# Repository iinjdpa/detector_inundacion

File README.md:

# detector_inundacion
Detector de inundacion con ESP8266 usando pilas

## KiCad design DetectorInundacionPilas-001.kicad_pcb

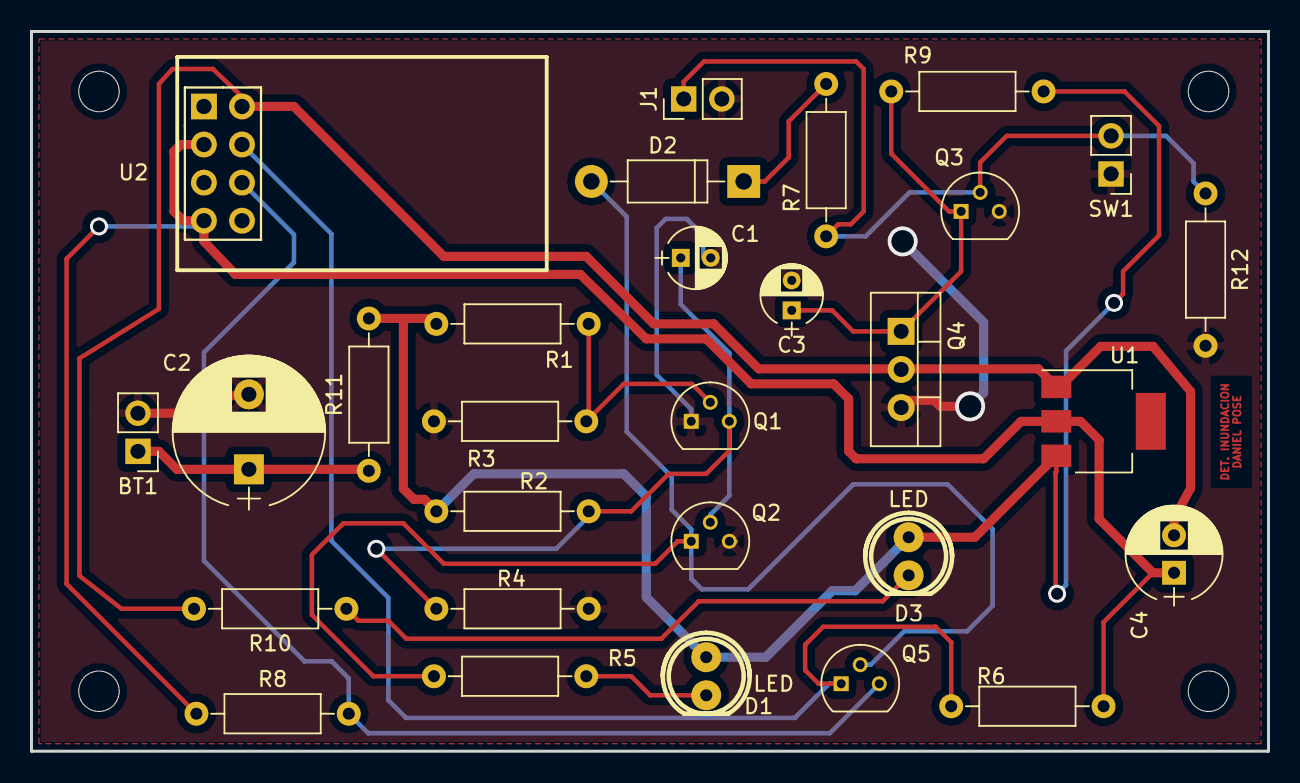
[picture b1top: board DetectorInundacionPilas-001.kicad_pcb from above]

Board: 2 copper layers, 82.5 x 48.0 mm, 29 parts (0 on the bottom side), 15 nets.

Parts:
BT1: 4xAA; Pin_Header_Straight_1x02_Pitch2.54mm
C1: 100uF; CP_Radial_D4.0mm_P2.00mm
C2: 1000uF; CP_Radial_D10.0mm_P5.00mm
C3: 0.1uF; CP_Radial_D4.0mm_P2.00mm
C4: 470uF; CP_Radial_D6.3mm_P2.50mm
D1: LED; led_5mm_red
D2: 1N4007; D_DO-41_SOD81_P10.16mm_Horizontal
D3: LED; led_5mm_green
J1: Sensor agua; Pin_Header_Straight_1x02_Pitch2.54mm
Q1: 2N7000; TO-92_Molded_Narrow
Q2, Q3, Q5: BS170; TO-92_Molded_Narrow
Q4: IRFZ44; TO-220-3_Vertical
R1: 270K; R_Axial_DIN0207_L6.3mm_D2.5mm_P10.16mm_Horizontal
R2, R3: 100K; R_Axial_DIN0207_L6.3mm_D2.5mm_P10.16mm_Horizontal
R4: 1M; R_Axial_DIN0207_L6.3mm_D2.5mm_P10.16mm_Horizontal
R5: 470; R_Axial_DIN0207_L6.3mm_D2.5mm_P10.16mm_Horizontal
R6, R8: 4K7; R_Axial_DIN0207_L6.3mm_D2.5mm_P10.16mm_Horizontal
R7: 10K; R_Axial_DIN0207_L6.3mm_D2.5mm_P10.16mm_Horizontal
R9: 470K; R_Axial_DIN0207_L6.3mm_D2.5mm_P10.16mm_Horizontal
R10: 1K; R_Axial_DIN0207_L6.3mm_D2.5mm_P10.16mm_Horizontal
R11: 3.3; R_Axial_DIN0207_L6.3mm_D2.5mm_P10.16mm_Horizontal
R12: 220K; R_Axial_DIN0207_L6.3mm_D2.5mm_P10.16mm_Horizontal
SW1: Test Button; Pin_Header_Straight_1x02_Pitch2.54mm
U1: AMS1117-3.3; SOT-223
U2: ESP-01v090; ESP-01

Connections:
/CP1: D1.1, D3.1, R1.1, R2.1, R9.1, R11.2, U1.3
/CPG: Q5.3, R8.2, U2.6
/CPS: D2.2, Q2.1, Q5.2, R5.2
/CPT: Q5.1, R6.2, U2.4
/DET1: J1.1, Q3.2, R7.2, R12.1, SW1.2
/ES1: C4.2, Q4.2, R10.2, U1.1, U2.2
/ES2: C4.1, R6.1, R8.1, U1.2, U2.3, U2.7
Earth: BT1.2, C1.2, C2.2, C3.2, J1.2, Q1.1, Q2.3, Q3.3, Q4.3, R3.2, R4.2, R12.2, SW1.1
unnamed: BT1.1, C2.1, R11.1
unnamed: C1.1, Q1.3, Q2.2, R2.2, R4.1
unnamed: C3.1, Q3.1, Q4.1, R9.2
unnamed: D1.2, R5.1
unnamed: D2.1, R7.1
unnamed: D3.2, R10.1
unnamed: Q1.2, R1.2, R3.1

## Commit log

2018-03-03 imagenes proyecto terminado
